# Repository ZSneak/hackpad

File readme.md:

# zhackpad

*A short description of the keyboard/project*

* Keyboard Maintainer: [ZSneak](https://github.com/ZSneak)
* Hardware Supported: *The PCBs, controllers supported*
* Hardware Availability: *Links to where you can find this hardware*

Make example for this keyboard (after setting up your build environment):

    make zhackpad:default

Flashing example for this keyboard:

    make zhackpad:default:flash

See the [build environment setup](https://docs.qmk.fm/#/getting_started_build_tools) and the [make instructions](https://docs.qmk.fm/#/getting_started_make_guide) for more information. Brand new to QMK? Start with our [Complete Newbs Guide](https://docs.qmk.fm/#/newbs).

## Bootloader

Enter the bootloader in 3 ways:

* **Bootmagic reset**: Hold down the key at (0,0) in the matrix (usually the top left key or Escape) and plug in the keyboard
* **Physical reset button**: Briefly press the button on the back of the PCB - some may have pads you must short instead
* **Keycode in layout**: Press the key mapped to `QK_BOOT` if it is available
# hackpad
*Note:* **the firmwear is not garunteed to be 100% functional yet. when i am able to recieve the hackpad itself and build it, and make sure the firmware can run, I wil reupload the github with the updated and correct firmware**

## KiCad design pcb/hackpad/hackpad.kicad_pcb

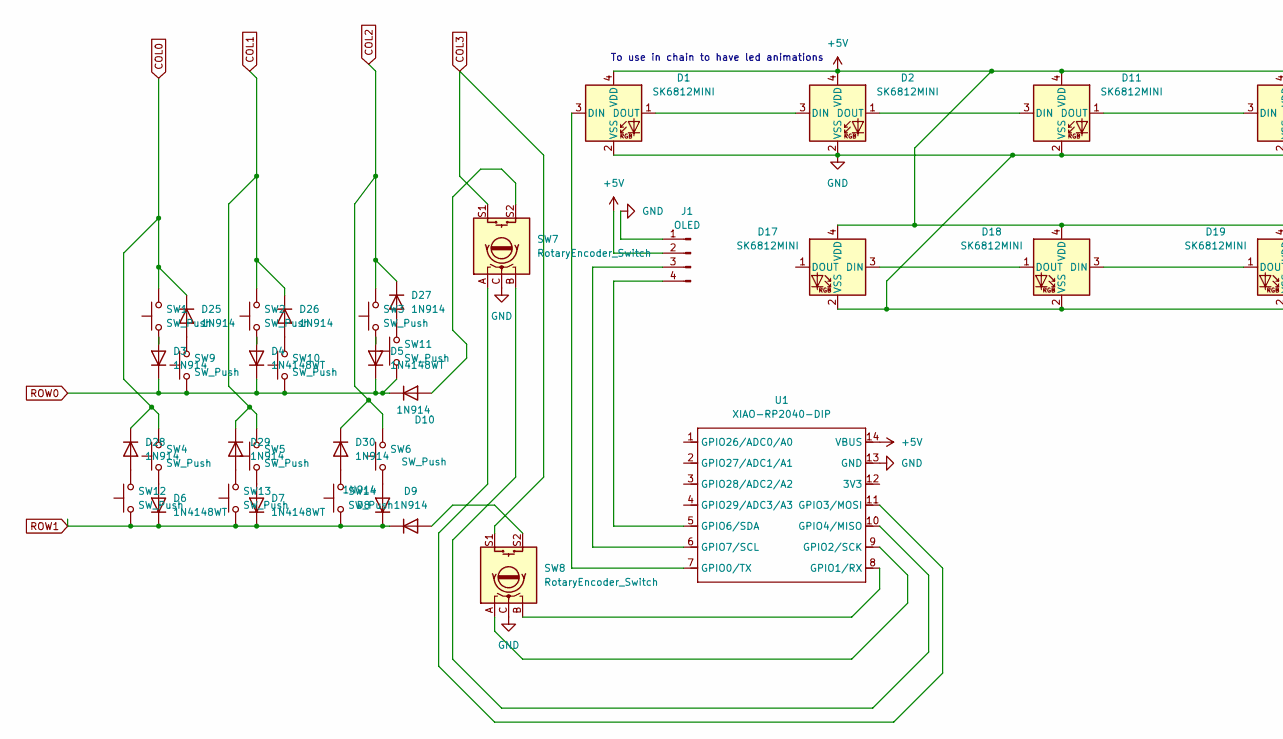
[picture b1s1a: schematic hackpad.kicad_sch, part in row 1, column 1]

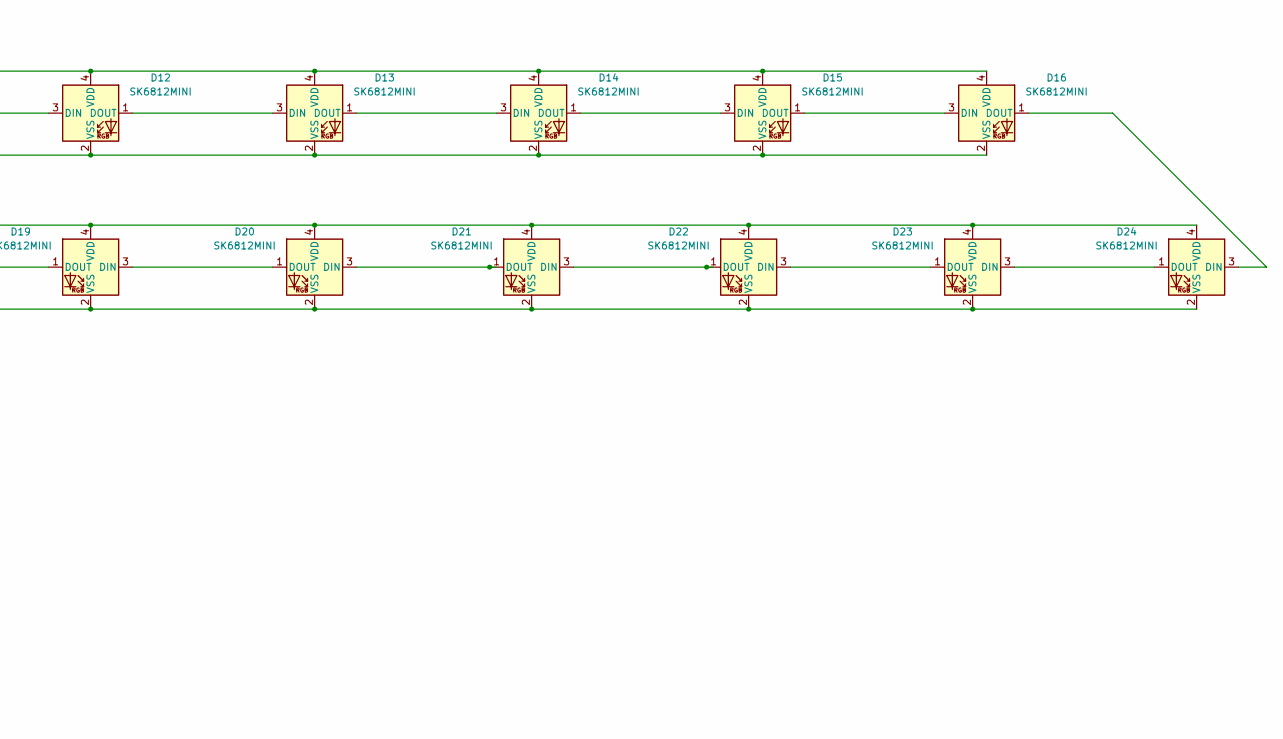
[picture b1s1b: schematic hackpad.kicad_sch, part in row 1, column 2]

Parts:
D1, D2, D11, D12, D13, D14, D15, D16, D17, D18, D19, D20, D21, D22, D23, D24: SK6812MINI; LED_SK6812MINI_PLCC4_3.5x3.5mm_P1.75mm
D3, D8, D9, D10, D25, D26, D27, D28, D29, D30: 1N914; D_DO-35_SOD27_P7.62mm_Horizontal
D4, D5, D6, D7: 1N4148WT; D_DO-35_SOD27_P7.62mm_Horizontal
J1: OLED; SSD1306-0.91-OLED-4pin-128x32
SW1, SW2, SW3, SW4, SW5, SW6, SW9, SW10, SW11, SW12, SW13, SW14: SW_Push; SW_Cherry_MX_1.00u_PCB
SW7, SW8: RotaryEncoder_Switch; RotaryEncoder_Alps_EC11E-Switch_Vertical_H20mm
U1: XIAO-RP2040-DIP

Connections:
+5V: D1.4 (VDD), D2.4 (VDD), D11.4 (VDD), D12.4 (VDD), D13.4 (VDD), D14.4 (VDD), D15.4 (VDD), D16.4 (VDD), D17.4 (VDD), D18.4 (VDD), D19.4 (VDD), D20.4 (VDD), D21.4 (VDD), D22.4 (VDD), D23.4 (VDD), D24.4 (VDD), J1.2, U1.14 (VBUS)
COL0: D25.1 (K), D28.1 (K), SW1.2, SW4.2
COL1: D26.1 (K), D29.1 (K), SW2.2, SW5.2
COL2: D27.1 (K), D30.1 (K), SW3.2, SW6.2
COL3: SW7.S1, SW8.S1
GND: D1.2 (VSS), D2.2 (VSS), D11.2 (VSS), D12.2 (VSS), D13.2 (VSS), D14.2 (VSS), D15.2 (VSS), D16.2 (VSS), D17.2 (VSS), D18.2 (VSS), D19.2 (VSS), D20.2 (VSS), D21.2 (VSS), D22.2 (VSS), D23.2 (VSS), D24.2 (VSS), J1.1, SW7.C, SW8.C, U1.13 (GND)
unnamed: D1.3 (DIN), U1.7 (GPIO0/TX)
unnamed: D1.1 (DOUT), D2.3 (DIN)
unnamed: D3.2 (A), SW1.1
unnamed: D4.2 (A), SW2.1
unnamed: D5.2 (A), SW3.1
unnamed: D6.2 (A), SW4.1
unnamed: D7.2 (A), SW5.1
unnamed: D8.2 (A), SW6.1
unnamed: D9.2 (A), SW8.S2
unnamed: D10.2 (A), SW7.S2
unnamed: D2.1 (DOUT), D11.3 (DIN)
unnamed: D11.1 (DOUT), D12.3 (DIN)
unnamed: D12.1 (DOUT), D13.3 (DIN)
unnamed: D13.1 (DOUT), D14.3 (DIN)
unnamed: D14.1 (DOUT), D15.3 (DIN)
unnamed: D15.1 (DOUT), D16.3 (DIN)
unnamed: D16.1 (DOUT), D24.3 (DIN)
unnamed: D17.3 (DIN), D18.1 (DOUT)
unnamed: D18.3 (DIN), D19.1 (DOUT)
unnamed: D19.3 (DIN), D20.1 (DOUT)
unnamed: D20.3 (DIN), D21.1 (DOUT)
unnamed: D21.3 (DIN), D22.1 (DOUT)
unnamed: D22.3 (DIN), D23.1 (DOUT)
unnamed: D23.3 (DIN), D24.1 (DOUT)
unnamed: D25.2 (A), SW9.2
unnamed: D26.2 (A), SW10.2
unnamed: D27.2 (A), SW11.2
unnamed: D28.2 (A), SW12.2
unnamed: D29.2 (A), SW13.2
unnamed: D30.2 (A), SW14.2
unnamed: J1.3, U1.6 (GPIO7/SCL)
unnamed: J1.4, U1.5 (GPIO6/SDA)
unnamed: SW8.B, U1.8 (GPIO1/RX)
unnamed: SW8.A, U1.9 (GPIO2/SCK)
unnamed: SW7.A, U1.11 (GPIO3/MOSI)
unnamed: SW7.B, U1.10 (GPIO4/MISO)
ROW0: D3.1 (K), D4.1 (K), D5.1 (K), D10.1 (K), SW9.1, SW10.1, SW11.1
ROW1: D6.1 (K), D7.1 (K), D8.1 (K), D9.1 (K), SW12.1, SW13.1, SW14.1

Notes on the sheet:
To use in chain to have led animations

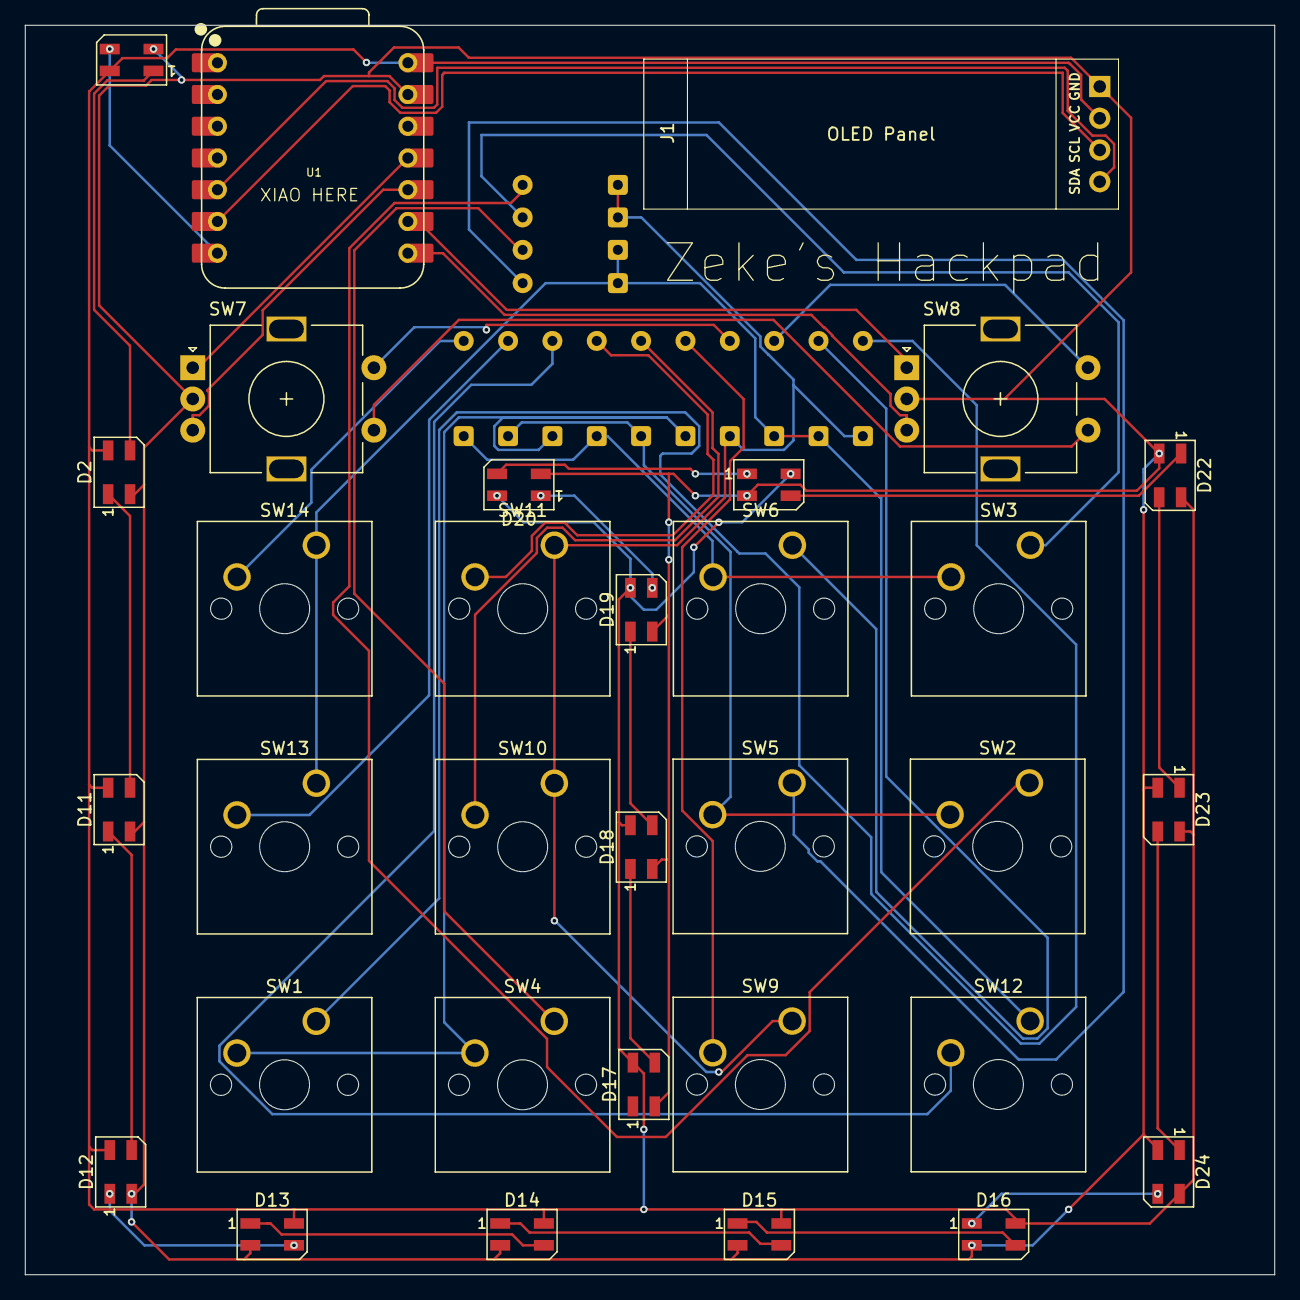
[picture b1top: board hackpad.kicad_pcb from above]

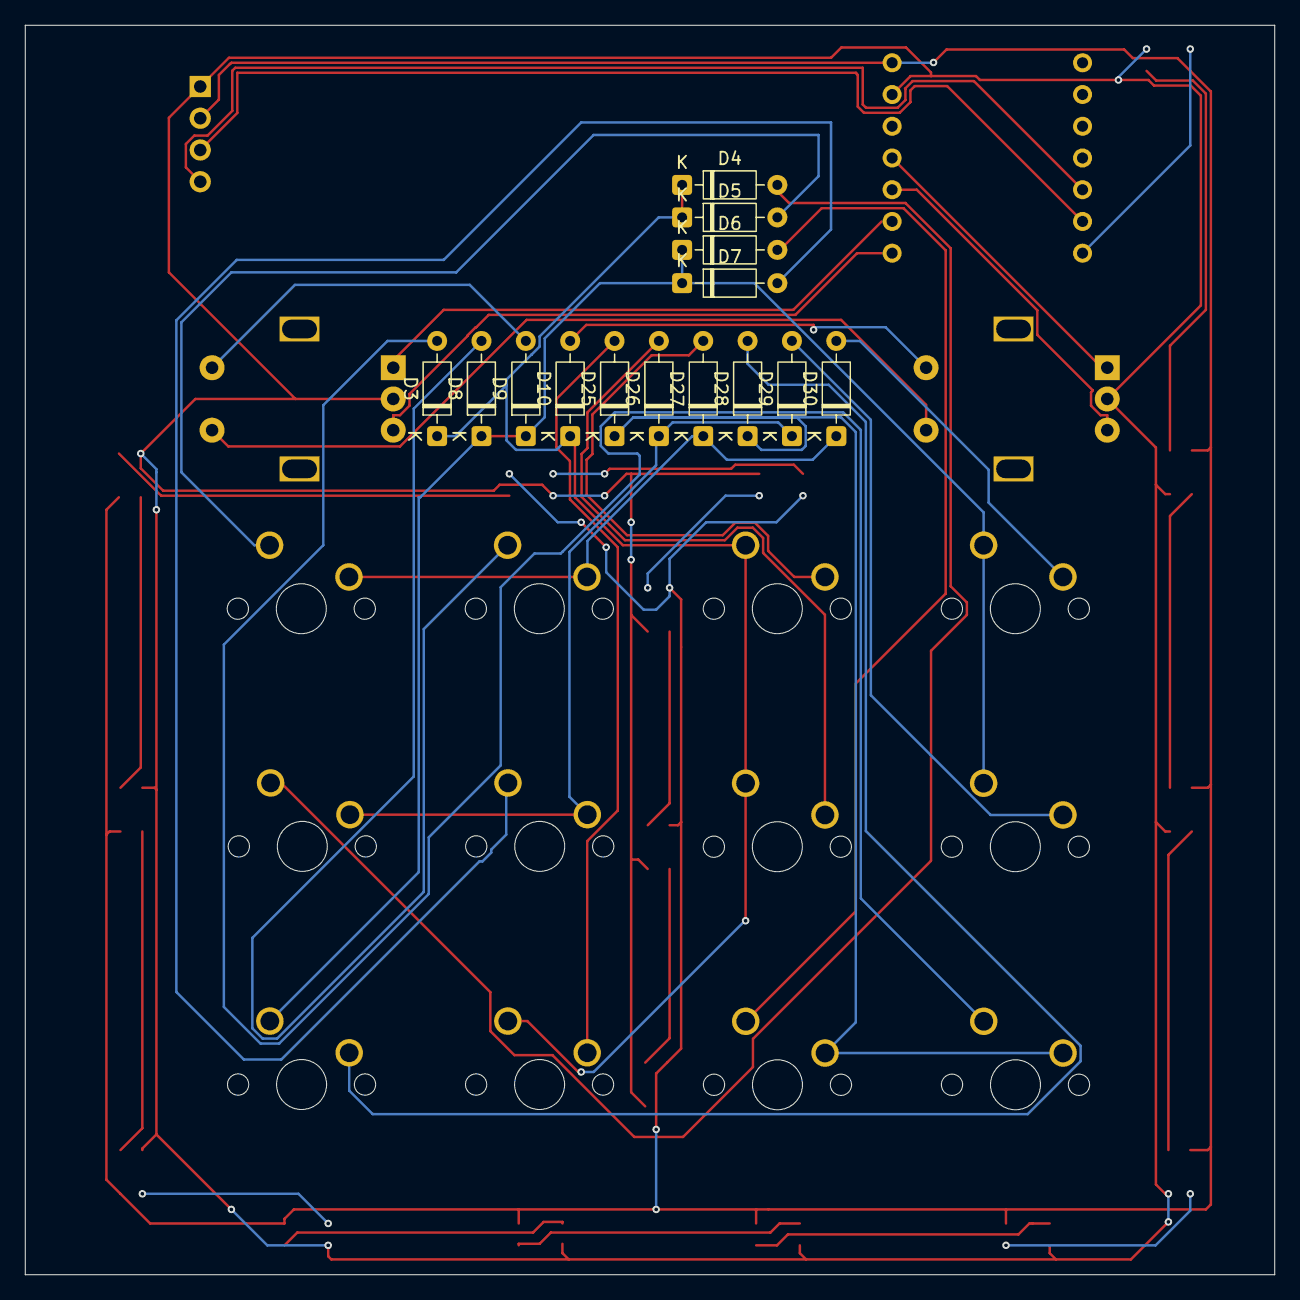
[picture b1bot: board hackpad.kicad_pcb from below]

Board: 2 copper layers, 100.0 x 100.0 mm, 46 parts (14 on the bottom side), 44 nets.

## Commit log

2026-02-25 initial
2026-02-25 put all of the files
2026-02-25 moved readme
2026-03-10 Update README with firmware functionality note
    Added a note about firmware functionality and future updates.
2026-03-31 added prod folder and step
2026-03-31 added other prod stuff
